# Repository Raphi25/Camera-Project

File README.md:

# Camera-Project
This master's project investigates the development of a low-cost wearable camera system intended to support caregivers by capturing images throughout the wearer's daily life. The system can take images in 30 second intervals in different settings while remaining lightweight, robust, serviceable, inexpensive and long battery life.

## Current firmware and shared App

The current firmware is in [Development Board Prototype/Code](Development%20Board%20Prototype/Code) and [Breadboard Prototype/Code](Breadboard%20Prototype/Code). Open either Code folder and build with `idf.py build`. Dependencies are restored by the ESP-IDF component manager; generated build output and Python environments are excluded.

Both projects use the single [App](App) folder. The packaged Windows application, [GUI.exe](App/GUI.exe), is included in the repository; use `Launch_GUI.cmd` to run it. To run from source, use `Setup_App.cmd` and `Launch_Source.cmd`, or rebuild the executable with `Build_GUI_App.cmd`. Each firmware folder also has launch and build shortcuts to the shared App. Local passwords and settings are not part of the repository.

## Architecture

Explore the system, firmware, and desktop application interactively:

[Open the interactive architecture explorer](https://raphi25.github.io/Camera-Project/project-architecture.html)

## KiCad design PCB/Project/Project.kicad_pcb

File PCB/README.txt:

This folder contains the Schematic, PCB design and BOM of the device, as well as the datasheets of the parts used for the PCB.

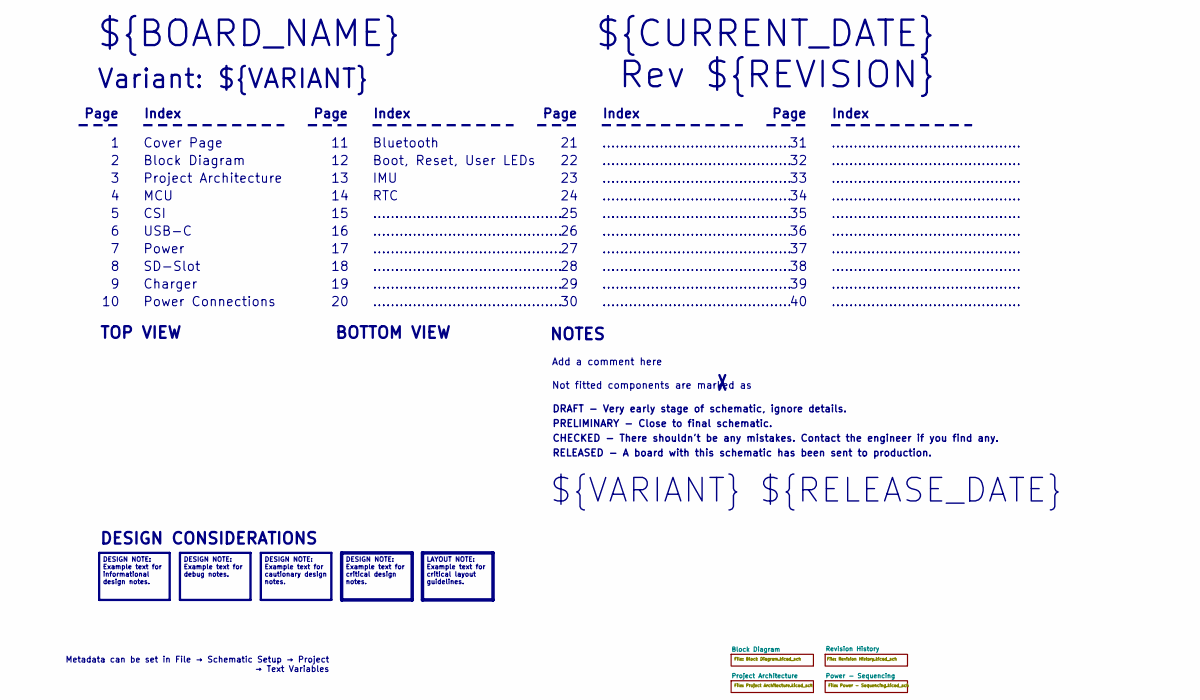
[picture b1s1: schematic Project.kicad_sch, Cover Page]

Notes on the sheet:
Metadata can be set in File → Schematic Setup → Project → Text Variables
DESIGN NOTE: Example text for informational design notes.
LAYOUT NOTE: Example text for critical layout guidelines.
DESIGN NOTE: Example text for cautionary design notes.
DESIGN NOTE: Example text for debug notes.
DESIGN NOTE: Example text for critical design notes.
BOTTOM VIEW
...........................................
RELEASED - A board with this schematic has been sent to production.
Page
TOP VIEW
Power Connections
Charger
SD-Slot
Not fitted components are marked as
Index
IMU
PRELIMINARY - Close to final schematic.
${VARIANT} ${RELEASE_DATE}
MCU
${CURRENT_DATE}
Variant: ${VARIANT}
Rev ${REVISION}
CSI
Bluetooth
${BOARD_NAME}
DRAFT - Very early stage of schematic, ignore details.
RTC
USB-C
Block Diagram
Add a comment here
Cover Page
NOTES
Boot, Reset, User LEDs
Project Architecture
CHECKED - There shouldn't be any mistakes. Contact the engineer if you find any.
DESIGN CONSIDERATIONS
Power

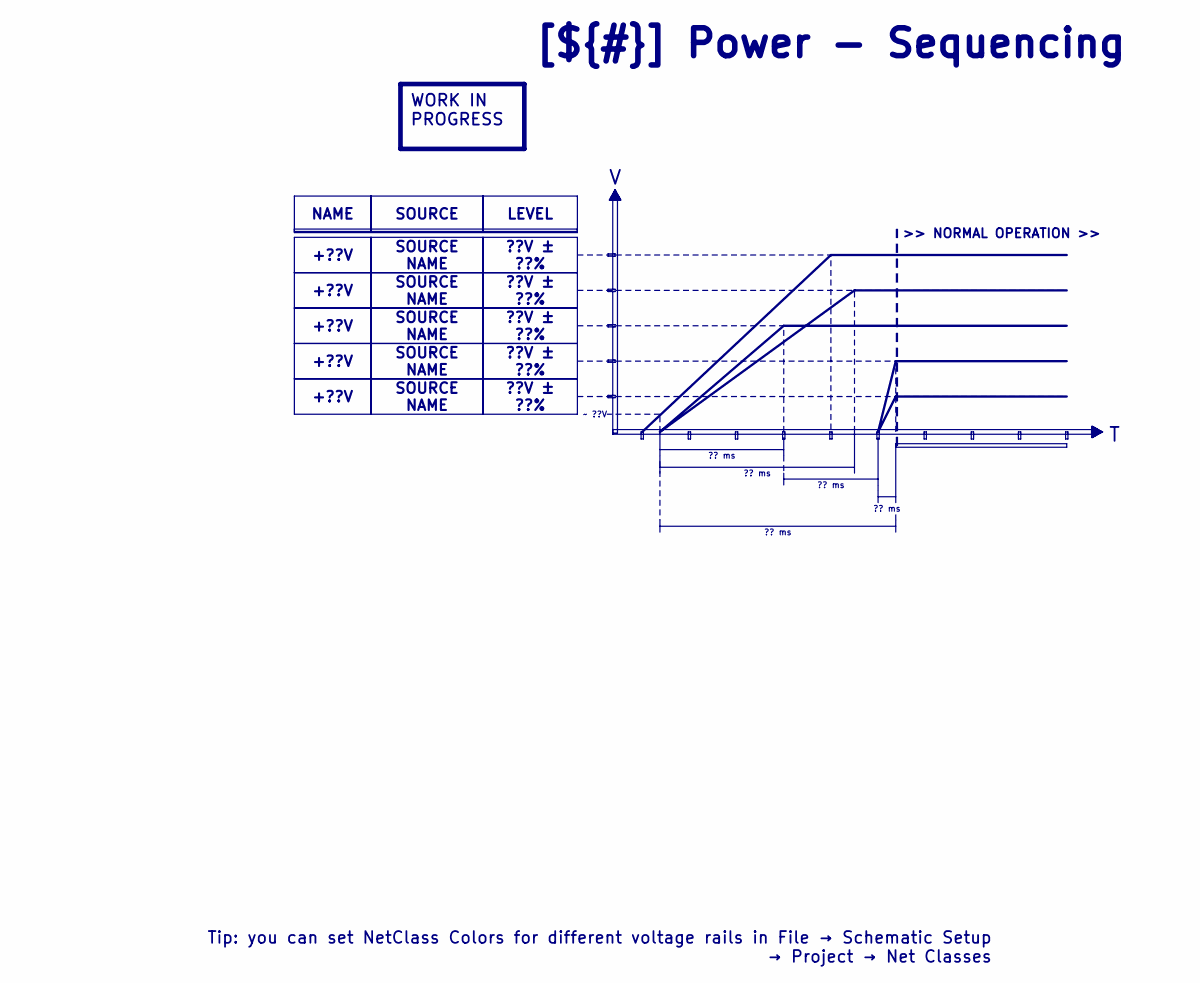
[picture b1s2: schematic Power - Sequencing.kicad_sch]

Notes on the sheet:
LEVEL
+??V
SOURCE NAME
?? ms
??V ± ??%
WORK IN PROGRESS
[${#}] ${TITLE}
~ ??V
NAME
SOURCE
Tip: you can set NetClass Colors for different voltage rails in File → Schematic Setup → Project → Net Classes
>> NORMAL OPERATION >>

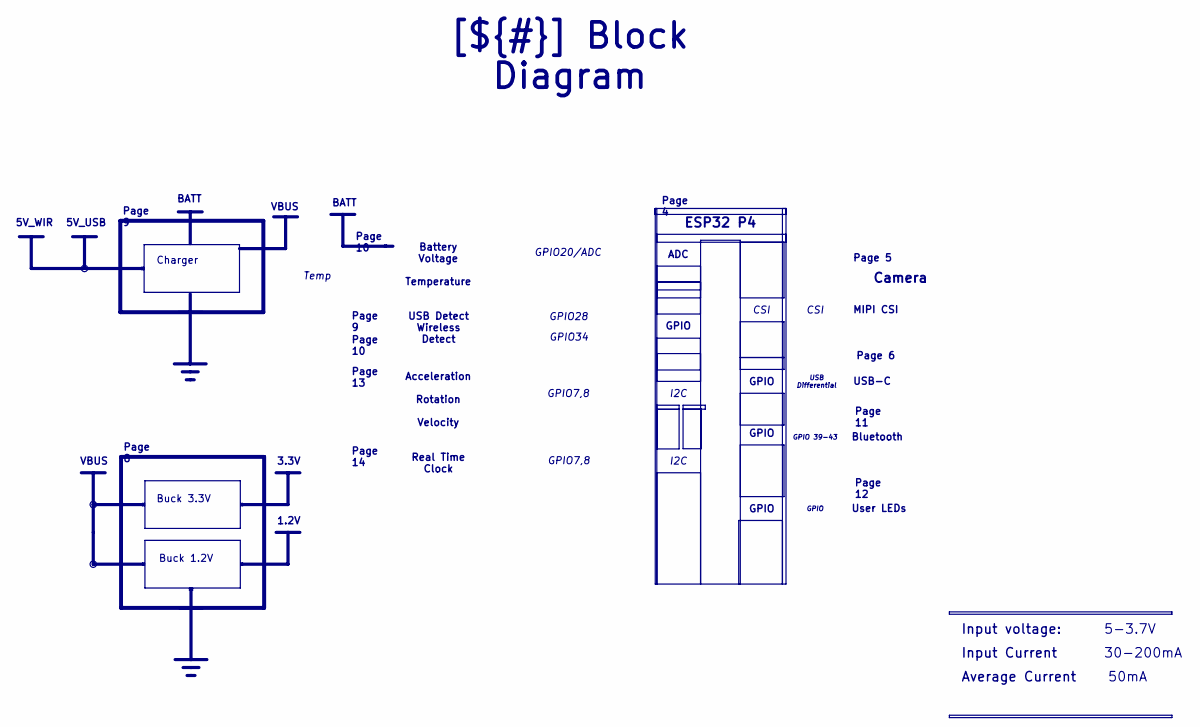
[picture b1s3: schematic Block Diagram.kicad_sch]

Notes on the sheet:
Charger
Bluetooth
Average Current
5V_WIR
Buck 3.3V
Input Current
Page 10
GPIO28
ESP32 P4
GPIO7,8
GPIO
Page 4
Page 14
ADC
Page 5
CSI
Page 11
Input voltage:
GPIO20/ADC
50mA
Page 12
30-200mA
Acceleration Rotation Velocity
USB Differential
Page 6
Camera
Buck 1.2V
Battery Voltage Temperature
3.3V
GPIO 39-43
VBUS
USB-C
GPIO34
Page 8
MIPI CSI
BATT
Temp
[${#}] ${TITLE}
Real Time Clock
Page 9

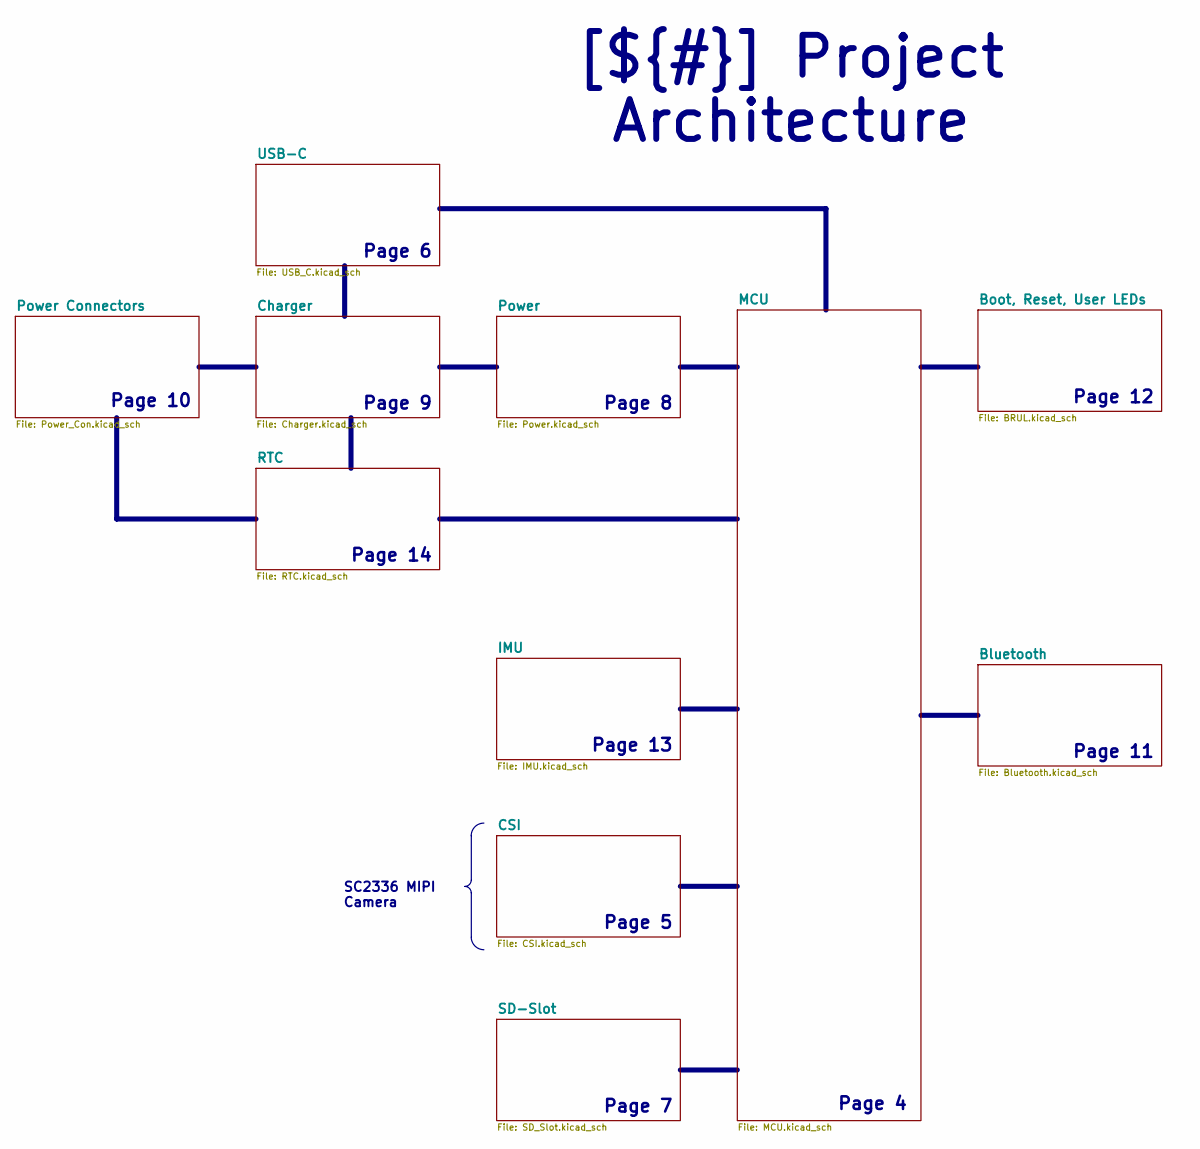
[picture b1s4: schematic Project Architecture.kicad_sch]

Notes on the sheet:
[${#}] ${TITLE}
SC2336 MIPI Camera
Page 13
Page 6
Page 10
Page 11
Page 14
Page 12
Page 4
Page 7
Page 5
Page 8
Page 9

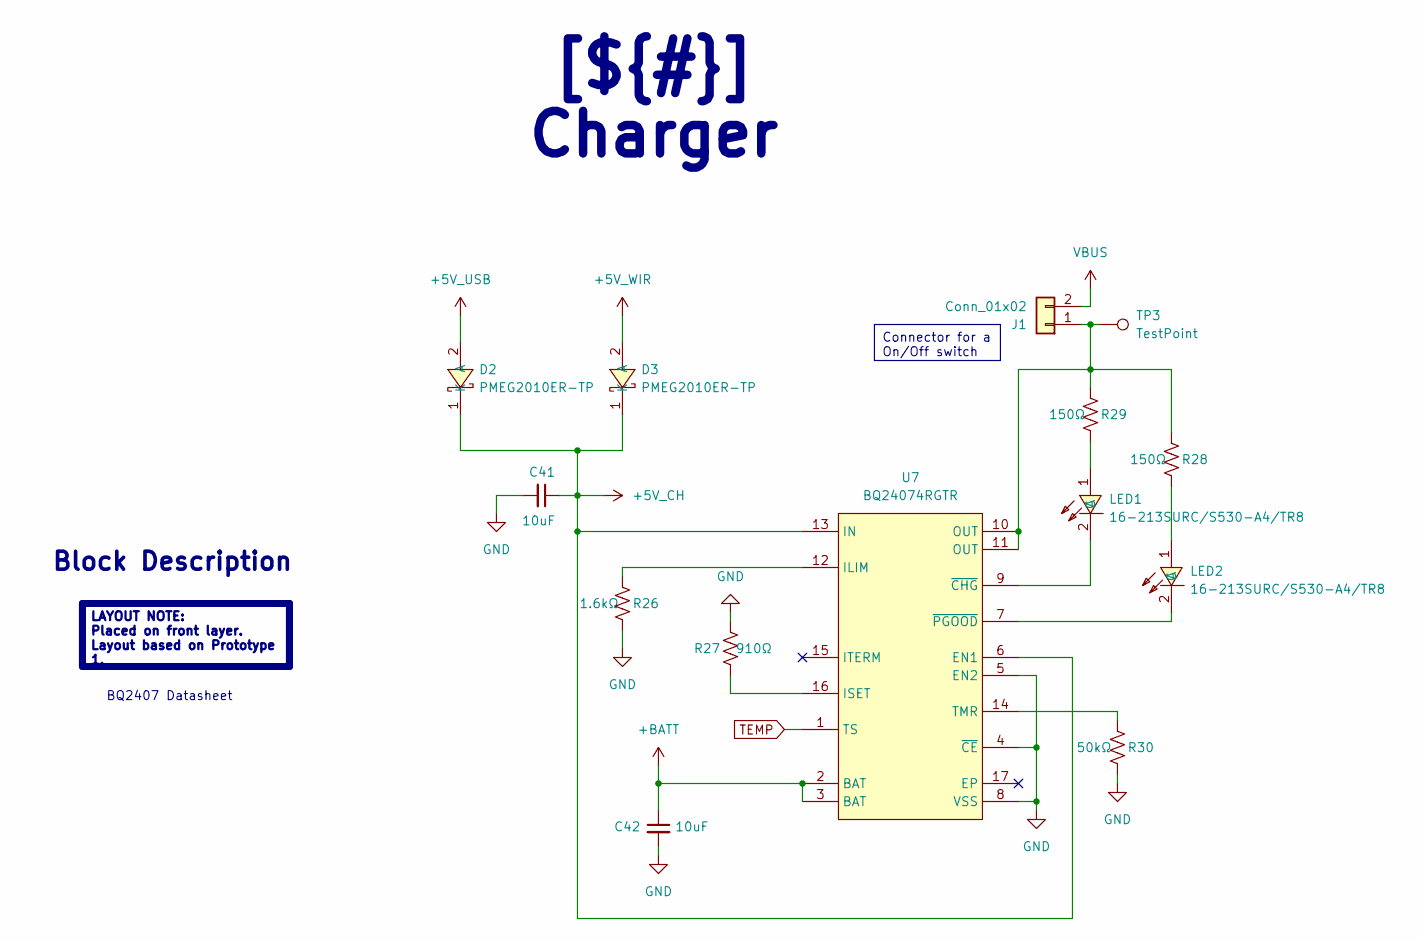
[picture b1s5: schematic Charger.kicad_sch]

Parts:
C41, C42: 10uF; C_0402_1005Metric
D2, D3: PMEG2010ER-TP; SOD-123F_L2.7-W1.7-LS3.6-RD; MPN PMEG2010ER-TP; LCSC Part C49231019
J1: Conn_01x02; SolderWire-0.1sqmm_1x02_P3.6mm_D0.4mm_OD1mm
LED1, LED2: 16-213SURC/S530-A4/TR8; LED0402-R-RD; MPN 16-213SURC/S530-A4/TR8; LCSC Part C74339
R26: 1.6kΩ; R_0402_1005Metric
R27: 910Ω; R_0402_1005Metric
R28, R29: 150Ω; R_0402_1005Metric
R30: 50kΩ; R_0402_1005Metric
TP3: TestPoint; TestPoint_Pad_1.0x1.0mm
U7: BQ24074RGTR; QFN-16_L3.0-W3.0-P0.50-TL-EP1.7; MPN BQ24074RGTR; LCSC Part C54313

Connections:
+5V_CH: C41.1, D2.1 (K), D3.1 (K), U7.6 (EN1), U7.13 (IN); also elsewhere on the board
+5V_USB: D2.2 (A); also elsewhere on the board
+5V_WIR: D3.2 (A); also elsewhere on the board
+BATT: C42.1, U7.2 (BAT), U7.3 (BAT); also elsewhere on the board
GND: C41.2, C42.2, R26.2, R27.2, R30.2, U7.4 (~CE), U7.5 (EN2), U7.8 (VSS); also elsewhere on the board
unnamed 41: J1.1, R28.1, R29.1, TP3.1, U7.10 (OUT), U7.11 (OUT); also elsewhere on the board
unnamed: LED1.1 (A), R29.2
unnamed 45: LED1.2 (C), U7.9 (~CHG); also elsewhere on the board
unnamed: LED2.1 (A), R28.2
unnamed 47: LED2.2 (C), U7.7 (~PGOOD); also elsewhere on the board
unnamed 61: R26.1, U7.12 (ILIM); also elsewhere on the board
unnamed 62: R27.1, U7.16 (ISET); also elsewhere on the board
unnamed 63: R30.1, U7.14 (TMR); also elsewhere on the board

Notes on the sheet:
[${#}] ${TITLE}
Connector for a On/Off switch
Block Description
LAYOUT NOTE: Placed on front layer. Layout based on Prototype 1.
BQ2407 Datasheet

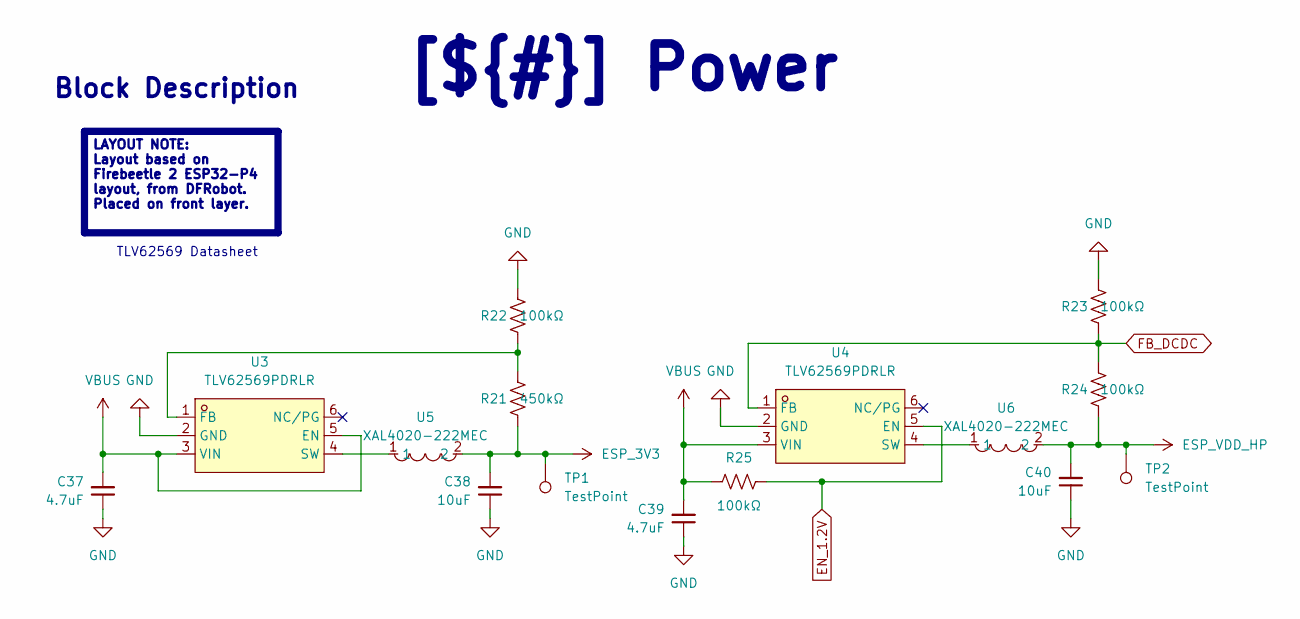
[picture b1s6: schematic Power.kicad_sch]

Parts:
C37, C39: 4.7uF; C_0402_1005Metric
C38, C40: 10uF; C_0402_1005Metric
R21: 450kΩ; R_0402_1005Metric
R22, R23, R24, R25: 100kΩ; R_0402_1005Metric
TP1, TP2: TestPoint; TestPoint_Pad_1.0x1.0mm
U3, U4: TLV62569PDRLR; SOT-563_L1.6-W1.2-P0.50-LS1.6-BL; MPN TLV62569PDRLR; LCSC Part C398364
U5, U6: XAL4020-222MEC; IND-SMD_L4.0-W4.0-A; MPN XAL4020-222MEC; LCSC Part C3151182

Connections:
EN_1.2V: R25.2, U4.5 (EN); also elsewhere on the board
ESP_3V3: C38.2, R21.1, TP1.1, U5.2; also elsewhere on the board
ESP_VDD_HP: C40.2, R24.1, TP2.1, U6.2; also elsewhere on the board
FB_DCDC: R23.1, R24.2, U4.1 (FB); also elsewhere on the board
GND: C37.1, C38.1, C39.1, C40.1, R22.2, R23.2, U3.2 (GND), U4.2 (GND); also elsewhere on the board
unnamed 58: R21.2, R22.1, U3.1 (FB); also elsewhere on the board
unnamed 59: U3.4 (SW), U5.1; also elsewhere on the board
unnamed 60: U4.4 (SW), U6.1; also elsewhere on the board
VBUS: C37.2, C39.2, R25.1, U3.3 (VIN), U3.5 (EN), U4.3 (VIN); also elsewhere on the board

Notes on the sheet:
[${#}] ${TITLE}
Block Description
LAYOUT NOTE: Layout based on Firebeetle 2 ESP32-P4 layout, from DFRobot. Placed on front layer.
TLV62569 Datasheet

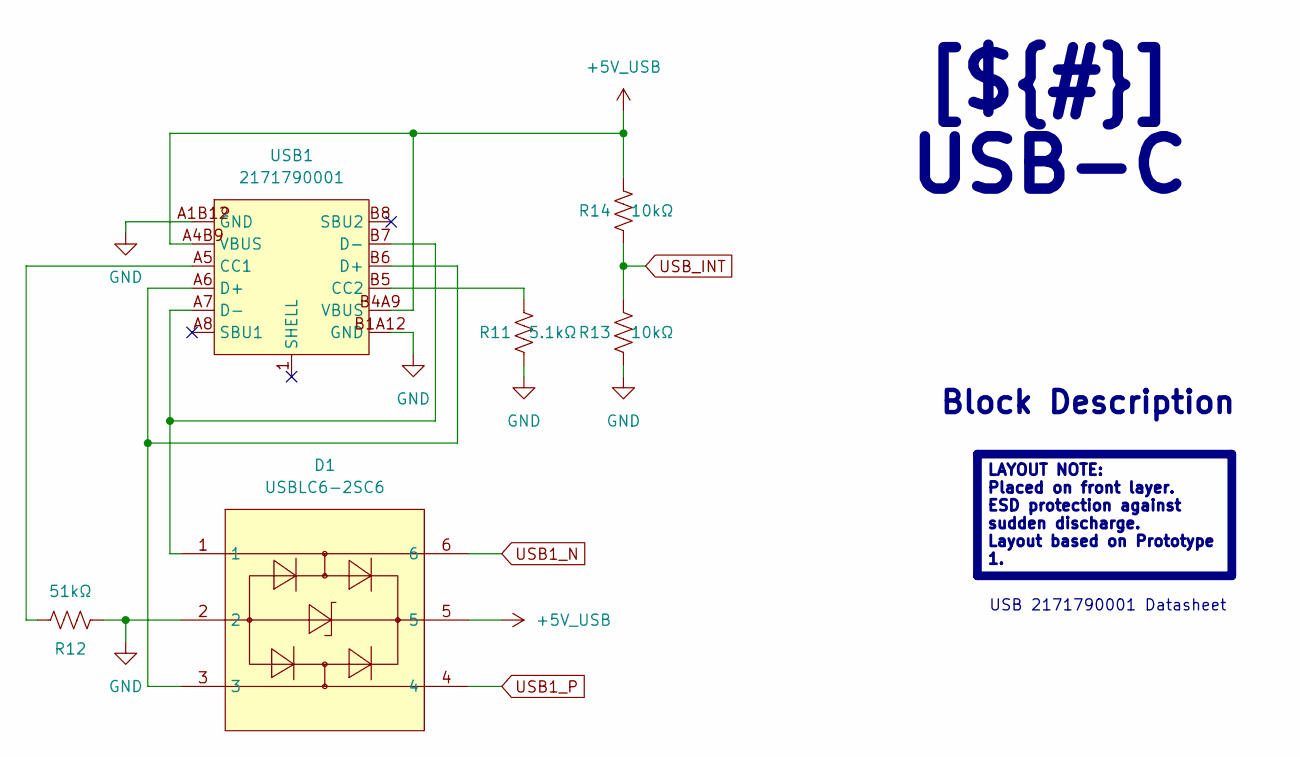
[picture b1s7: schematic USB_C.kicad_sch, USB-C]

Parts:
D1: USBLC6-2SC6; SOT-23-6_L2.9-W1.6-P0.95-LS2.8-BL; MPN USBLC6-2SC6; LCSC Part C7519
R11: 5.1kΩ; R_0402_1005Metric
R12: 51kΩ; R_0402_1005Metric
R13, R14: 10kΩ; R_0402_1005Metric
USB1: 2171790001; USB-C-SMD_2171790001; MPN 2171790001; LCSC Part C3197684

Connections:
+5V_USB: D1.5, R14.2, USB1.A4B9 (VBUS), USB1.B4A9 (VBUS); also elsewhere on the board
GND: D1.2, R11.1, R12.1, R13.1, USB1.A1B12 (GND), USB1.B1A12 (GND); also elsewhere on the board
unnamed: D1.1, USB1.A7 (D-), USB1.B7 (D-)
unnamed: D1.3, USB1.A6 (D+), USB1.B6 (D+)
unnamed: R12.2, USB1.A5 (CC1)
unnamed: R11.2, USB1.B5 (CC2)
USB1_N: D1.6; also elsewhere on the board
USB1_P: D1.4; also elsewhere on the board
USB_INT: R13.2, R14.1; also elsewhere on the board

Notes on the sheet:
Block Description
[${#}] ${TITLE}
LAYOUT NOTE: Placed on front layer. ESD protection against sudden discharge. Layout based on Prototype 1.
USB 2171790001 Datasheet

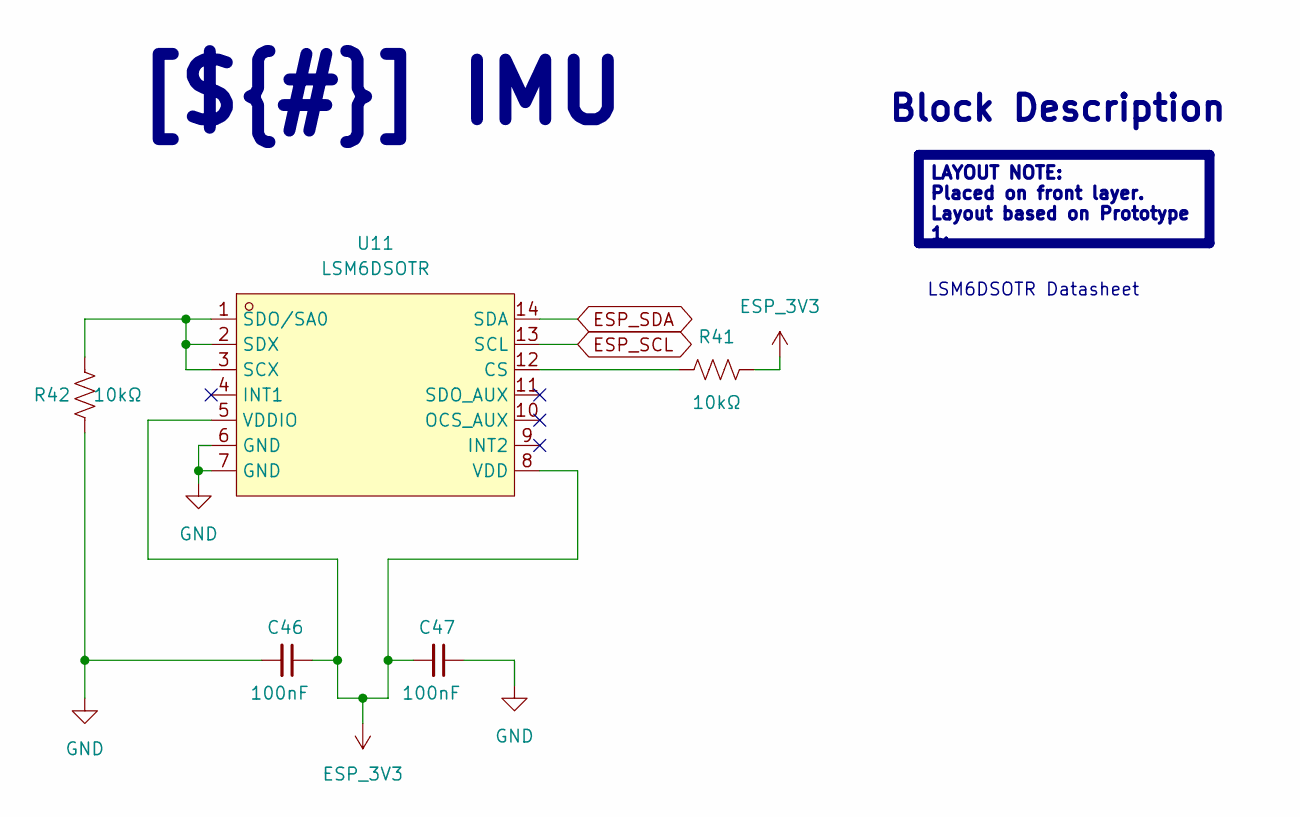
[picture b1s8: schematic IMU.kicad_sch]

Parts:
C46, C47: 100nF; C_0402_1005Metric
R41, R42: 10kΩ; R_0402_1005Metric
U11: LSM6DSOTR; LGA-14_L3.0-W2.5-P0.50-TL; MPN LSM6DSOTR; LCSC Part C2655100

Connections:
ESP_3V3: C46.1, C47.2, R41.2, U11.5 (VDDIO), U11.8 (VDD); also elsewhere on the board
GND: C46.2, C47.1, R42.1, U11.6 (GND), U11.7 (GND); also elsewhere on the board
unnamed 64: R41.1, U11.12 (CS); also elsewhere on the board
unnamed 65: R42.2, U11.1 (SDO/SA0), U11.2 (SDX), U11.3 (SCX); also elsewhere on the board

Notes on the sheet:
Block Description
LAYOUT NOTE: Placed on front layer. Layout based on Prototype 1.
[${#}] ${TITLE}
LSM6DSOTR Datasheet

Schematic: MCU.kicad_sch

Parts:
C1, C4: 10uF; C_0402_1005Metric
C2, C3, C5, C7, C9, C12, C14, C16, C21, C23, C24, C25, C27, C28, C31, C32, C33, C34: 100nF; C_0402_1005Metric
C6, C10, C13, C15, C17, C18, C19, C20, C22, C26: 1uF; C_0402_1005Metric
C8, C11: 10nF; C_0402_1005Metric
C29, C30: 18pF; C_0402_1005Metric
H1, H2, H3: MountingHole; MountingHole_3.2mm_M3
R1, R4, R5: 10kΩ; R_0402_1005Metric
R2, R3: 4.02kΩ; R_0402_1005Metric
U1: ESP32-P4NRW32X; QFN-104_L10.0-W10.0-P0.35-TL-EP7.5; MPN ESP32-P4NRW32X; LCSC Part C54540373
U2: W25Q128JVSIQ; SOIC127P790X216-8N; PARTREV I
Y1: Crystal_GND24_Small; Crystal_SMD_3225-4Pin_3.2x2.5mm

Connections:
BATT_MEASURE_USB: U1.22 (GPIO20); also elsewhere on the board
BOOT: U1.66 (GPIO35); also elsewhere on the board
C6_EN: U1.10 (GPIO9); also elsewhere on the board
C6_WAKEUP: U1.6 (GPIO6); also elsewhere on the board
CSI_CLK_N: U1.45 (CSI_CLKN); also elsewhere on the board
CSI_CLK_P: U1.44 (CSI_CLKP); also elsewhere on the board
CSI_D0_N: U1.42 (CSI_DATAN0); also elsewhere on the board
CSI_D0_P: U1.43 (CSI_DATAP0); also elsewhere on the board
CSI_D1_N: U1.46 (CSI_DATAN1); also elsewhere on the board
CSI_D1_P: U1.47 (CSI_DATAP1); also elsewhere on the board
CSI_PWR: U1.25 (GPIO23); also elsewhere on the board
DETECT_WIR: U1.65 (GPIO34); also elsewhere on the board
EN_1.2V: U1.79 (EN_DCDC); also elsewhere on the board
ESP_3V3: C1.1, C2.1, C3.1, C11.1, C12.1, C13.1, C16.2, C21.2, C22.1, C24.2, C28.2, C31.1, C32.1, R4.2, R5.2, U1.9 (VDD_LP), U1.21 (VDD_IO_0), U1.51 (VDD_USBPHY), U1.62 (VDD_IO_4), U1.75 (VDD_LDO), U1.77 (VDD_DCDCC), U1.96 (VDD_IO_6), U1.101 (VDD_ANA), U1.102 (VDD_BAT); also elsewhere on the board
ESP_LDO_VO1: C6.2, C7.2, C20.2, C34.1, R1.1, U1.30 (VDD_FLASHIO), U1.71 (VDDO_FLASH), U2.8 (VCC); also elsewhere on the board
ESP_LDO_VO2: C14.1, C15.2, C19.2, U1.59 (VDD_PSRAM_0), U1.67 (VDD_PSRAM_1), U1.72 (VDDO_PSRAM)
ESP_LDO_VO3: C8.1, C9.1, C10.1, C18.2, U1.41 (VDD_MIPI_DPHY), U1.73 (VDDO_3)
ESP_LDO_VO4: C17.2, C25.1, C26.2, U1.74 (VDDO_4), U1.85 (VDD_IO_5); also elsewhere on the board
ESP_SCL: U1.8 (GPIO8); also elsewhere on the board
ESP_SDA: U1.7 (GPIO7); also elsewhere on the board
ESP_VDD_HP: C4.1, C5.1, C23.2, C27.2, U1.26 (VDD_HP_0), U1.76 (VDD_HP_2), U1.91 (VDD_HP_3); also elsewhere on the board
FB_DCDC: U1.78 (FB_DCDC); also elsewhere on the board
FLASH_CK: U1.32 (FLASH_CK), U2.6 (CLK); also elsewhere on the board
FLASH_CS: R1.2, U1.27 (FLASH_CS), U2.1 (/CS); also elsewhere on the board
FLASH_D: U1.33 (FLASH_D), U2.5 (DI(IO0)); also elsewhere on the board
FLASH_HOLD: U1.31 (FLASH_HOLD), U2.7 (/HOLD/RESET(IO3)); also elsewhere on the board
FLASH_Q: U1.28 (FLASH_Q), U2.2 (DO(IO1)); also elsewhere on the board
FLASH_WP: U1.29 (FLASH_WP), U2.3 (/WP(IO2)); also elsewhere on the board
GND: C1.2, C2.2, C3.2, C4.2, C5.2, C6.1, C7.1, C8.2, C9.2, C10.2, C11.2, C12.2, C13.2, C14.2, C15.1, C16.1, C17.1, C18.1, C19.1, C20.1, C21.1, C22.2, C23.1, C24.1, C25.2, C26.1, C27.1, C28.1, C29.2, C30.2, C31.2, C32.2, C33.2, C34.2, R2.1, R3.1, U1.105 (GND), U2.4 (GND), Y1.2, Y1.4; also elsewhere on the board
unnamed: R3.2, U1.48 (CSI_REXT)
unnamed: R2.2, U1.34 (DSI_REXT)
unnamed: R4.1, U1.68 (GPIO36)
unnamed: C29.1, U1.99 (XTAL_N), Y1.3
unnamed: C30.1, U1.100 (XTAL_P), Y1.1
RESET: C33.1, R5.1, U1.103 (CHIP_PU); also elsewhere on the board
RTC_INT: U1.55 (GPIO26); also elsewhere on the board
SD1_CLK: U1.84 (GPIO43); also elsewhere on the board
SD1_CMD: U1.86 (GPIO44); also elsewhere on the board
SD1_D0: U1.80 (GPIO39); also elsewhere on the board
SD1_D1: U1.81 (GPIO40); also elsewhere on the board
SD1_D2: U1.82 (GPIO41); also elsewhere on the board
SD1_D3: U1.83 (GPIO42); also elsewhere on the board
SD1_PWRN: U1.3 (GPIO3); also elsewhere on the board
SDIO_CLK: U1.19 (GPIO18); also elsewhere on the board
SDIO_CMD: U1.20 (GPIO19); also elsewhere on the board
SDIO_D0: U1.15 (GPIO14); also elsewhere on the board
SDIO_D1: U1.16 (GPIO15); also elsewhere on the board
SDIO_D2: U1.17 (GPIO16); also elsewhere on the board
SDIO_D3: U1.18 (GPIO17); also elsewhere on the board
USB1_N: U1.52 (GPIO24); also elsewhere on the board
USB1_P: U1.53 (GPIO25); also elsewhere on the board
USB_INT: U1.57 (GPIO28); also elsewhere on the board
USER_LED_1: U1.1 (GPIO1); also elsewhere on the board
USER_LED_2: U1.2 (GPIO2); also elsewhere on the board

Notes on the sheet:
LAYOUT NOTE: Layout based on Firebeetle 2 ESP32-P4 layout, from DFRobot. Placed on front layer.
[${#}] ${TITLE}
Block Description
DESIGN NOTE: 40MHz, +-10ppm
Serial Flash Memory
W25Q128JVSIQ Datasheet
ESP32-P4 Datasheet

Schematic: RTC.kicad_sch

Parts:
C48: 1uF; C_0402_1005Metric
R43, R44, R45: 3.3kΩ; R_0402_1005Metric
U12: DS3231MZ+_C722467; SOIC-8_L4.9-W3.9-P1.27-LS6.0-BL; MPN DS3231MZ+; LCSC Part C722467

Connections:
+BATT2: C48.1, U12.6 (VBAT); also elsewhere on the board
ESP_3V3: R43.2, R44.2, R45.2; also elsewhere on the board
ESP_SCL: R43.1, U12.8 (SCL); also elsewhere on the board
ESP_SDA: R44.1, U12.7 (SDA); also elsewhere on the board
GND: C48.2, U12.5 (GND); also elsewhere on the board
RTC_INT: R45.1, U12.3 (~INT/SQW); also elsewhere on the board

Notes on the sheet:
Block Description
LAYOUT NOTE: Placed on back layer. Layout based on Prototype 1.
[${#}] ${TITLE}
DS3231MZ+ Datasheet

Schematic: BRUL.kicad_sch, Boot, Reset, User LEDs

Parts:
LED3, LED4, LED5: 16-213SURC/S530-A4/TR8; LED0402-R-RD; MPN 16-213SURC/S530-A4/TR8; LCSC Part C74339
R37: 330Ω; R_0402_1005Metric
R38, R39: 2.2kΩ; R_0402_1005Metric
R40: 4.7kΩ; R_0402_1005Metric
SW1, SW2: 1TS026A-1000-0550-CT; SW-SMD_4P-L2.6-W1.6-P0.75-LS3.0; MPN 1TS026A-1000-0550-CT; LCSC Part C913778

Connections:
BOOT: R40.1, SW2.3, SW2.4; also elsewhere on the board
ESP_3V3: R37.1, R40.2; also elsewhere on the board
GND: LED3.2 (C), LED4.2 (C), LED5.2 (C), SW1.1, SW1.2, SW2.1, SW2.2; also elsewhere on the board
unnamed: LED3.1 (A), R37.2
unnamed: LED4.1 (A), R38.2
unnamed: LED5.1 (A), R39.2
RESET: SW1.3, SW1.4; also elsewhere on the board
USER_LED_1: R38.1; also elsewhere on the board
USER_LED_2: R39.1; also elsewhere on the board

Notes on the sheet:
Block Description
LAYOUT NOTE: Layout based on Firebeetle 2 ESP32-P4 layout, from DFRobot. Placed on front layer.
TBD what to use them for
[${#}] ${TITLE}

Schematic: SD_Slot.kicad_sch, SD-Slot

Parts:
C49: 1uF; C_0402_1005Metric
C50: 100nF; C_0402_1005Metric
Q2: AO3401A_C306862; SOT-23-3_L2.9-W1.3-P1.90-LS2.4-BR; MPN AO3401A; LCSC Part C306862
R15: 51kΩ; R_0402_1005Metric
R16, R17, R18, R19, R20: 10kΩ; R_0402_1005Metric
SD1: 503398-1892; TF-SMD_503398-1892; MPN 5033981892; LCSC Part C428492

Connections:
ESP_3V3: Q2.2 (S); also elsewhere on the board
ESP_LDO_VO4: R16.1, R17.1, R18.1, R19.1, R20.1; also elsewhere on the board
GND: C49.1, C50.1, R15.2, SD1.6 (VSS); also elsewhere on the board
unnamed 52: C49.2, C50.2, Q2.3 (D), SD1.4 (VDD); also elsewhere on the board
SD1_CMD: R18.2, SD1.3 (CMD); also elsewhere on the board
SD1_D0: R19.2, SD1.7 (DAT0); also elsewhere on the board
SD1_D1: R20.2, SD1.8 (DAT1); also elsewhere on the board
SD1_D2: R16.2, SD1.1 (DAT2); also elsewhere on the board
SD1_D3: R17.2, SD1.2 (CD/DAT3); also elsewhere on the board
SD1_PWRN: Q2.1 (G), R15.1; also elsewhere on the board

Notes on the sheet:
[${#}] ${TITLE}
Block Description
LAYOUT NOTE: Layout based on Firebeetle 2 ESP32-P4 layout, from DFRobot. Placed on front layer.
Molex 503398-1892 Datasheet

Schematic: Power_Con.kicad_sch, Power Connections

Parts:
BAT1: 3000; BAT-SMD_CR1202; MPN 3000; LCSC Part C238097
JP1: SolderJumper_3_Bridged12; SolderJumper-3_P1.3mm_Bridged2Bar12_RoundedPad1.0x1.5mm
R31: 750Ω; R_0402_1005Metric
R32, R34: 10kΩ; R_0402_1005Metric
R33: 24.9kΩ; R_0402_1005Metric
R35: 15kΩ; R_0402_1005Metric
U8: SM03B-SRSS-TB; CONN-SMD_SM03B-SRSS-TB-LF-SN-P; MPN SM03B-SRSS-TB(LF)(SN); LCSC Part C160403
U9: S2B-PH-K-S; CONN-TH_S2B-PH-K-S-LF-SN; MPN S2B-PH-K-S(LF)(SN); LCSC Part C173752

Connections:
+5V_WIR: R34.2, U9.2; also elsewhere on the board
+BATT: R32.2, U8.1; also elsewhere on the board
BATT_MEASURE_USB: R32.1, R33.2; also elsewhere on the board
DETECT_WIR: R34.1, R35.2; also elsewhere on the board
GND: BAT1.3 (-), R31.1, R33.1, R35.1, U8.2, U9.1; also elsewhere on the board
unnamed: BAT1.1 (+), BAT1.2 (+)
unnamed 42: JP1.1 (A), U8.3; also elsewhere on the board
unnamed: JP1.3 (B), R31.2
TEMP: JP1.2 (C); also elsewhere on the board

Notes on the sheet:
LAYOUT NOTE: Placed on back layer. Layout based on Prototype 1.
Block Description
DFR0362
[${#}] ${TITLE}
RTC Battery Connector
Wireless Charger Connector
Battery Connector

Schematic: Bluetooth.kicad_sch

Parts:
C43, C45: 100nF; C_0402_1005Metric
C44: 10nF; C_0402_1005Metric
R36: 10kΩ; R_0402_1005Metric
U10: ESP32-C6-MINI-1-N4; WIFIM-SMD_61P-L16.6-W13.2-P0.80-ESP32-C6-MINI-1-N4; MPN ESP32-C6-MINI-1-N4; LCSC Part C5736265

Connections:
C6_EN: C45.1, R36.2, U10.8 (EN); also elsewhere on the board
ESP_3V3: C43.2, C44.2, R36.1, U10.3 (3V3); also elsewhere on the board
GND: C43.1, C44.1, C45.2, U10.1 (GND), U10.2 (GND), U10.11 (GND), U10.14 (GND), U10.36 (GND), U10.37 (GND), U10.38 (GND), U10.39 (GND), U10.40 (GND), U10.41 (GND), U10.42 (GND), U10.43 (GND), U10.44 (GND), U10.45 (GND), U10.46 (GND), U10.47 (GND), U10.48 (GND), U10.49 (GND), U10.50 (GND), U10.51 (GND), U10.52 (GND), U10.53 (GND); also elsewhere on the board

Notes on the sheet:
Block Description
LAYOUT NOTE: Layout based on Firebeetle 2 ESP32-P4 layout, from DFRobot. Placed on front layer.
[${#}] ${TITLE}
ESP32-C6-MINI-1 Datasheet

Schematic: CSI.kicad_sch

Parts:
C35: 100nF; C_0402_1005Metric
C36: 10nF; C_0402_1005Metric
FPC1: 1.0-15P下接; FPC-SMD_C66660; MPN 1.0-15P下接; LCSC Part C66660
Q1: AO3401A_C306862; SOT-23-3_L2.9-W1.3-P1.90-LS2.4-BR; MPN AO3401A; LCSC Part C306862
R6: 51kΩ; R_0402_1005Metric
R7, R8: 2.2kΩ; R_0402_1005Metric
R9, R10: 10kΩ; R_0402_1005Metric

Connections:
CSI_PWR: Q1.1 (G), R6.1; also elsewhere on the board
ESP_3V3: Q1.2 (S); also elsewhere on the board
GND: C35.1, C36.1, FPC1.1, FPC1.4, FPC1.7, FPC1.10, R6.2; also elsewhere on the board
unnamed 37: FPC1.11, R10.2; also elsewhere on the board
unnamed 38: FPC1.12, R9.2; also elsewhere on the board
unnamed 39: FPC1.13, R8.2; also elsewhere on the board
unnamed 40: FPC1.14, R7.2; also elsewhere on the board
unnamed 51: C35.2, C36.2, FPC1.15, Q1.3 (D), R7.1, R8.1, R9.1, R10.1; also elsewhere on the board

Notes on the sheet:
[${#}] ${TITLE}
Block Description
LAYOUT NOTE: Layout based on Firebeetle 2 ESP32-P4 layout, from DFRobot. Placed on front layer.
